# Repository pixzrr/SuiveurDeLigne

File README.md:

# SuiveurDeLigne

## Etape 1 : Créer le PCB
PCB : 100%

Carte imprimée

## Etape 2 : Soudure
Soudure : 100%

Tests : 8/9 validés (89%)

## Etape 3 : Programmation

Création des fonctions tests : terminé

Programmation en logique binaire (principe de sur-correction constante) : terminée

Programmation en logique analogique (s'adapter parfaitement à la courbe en fonction des nuances de gris) : en cours

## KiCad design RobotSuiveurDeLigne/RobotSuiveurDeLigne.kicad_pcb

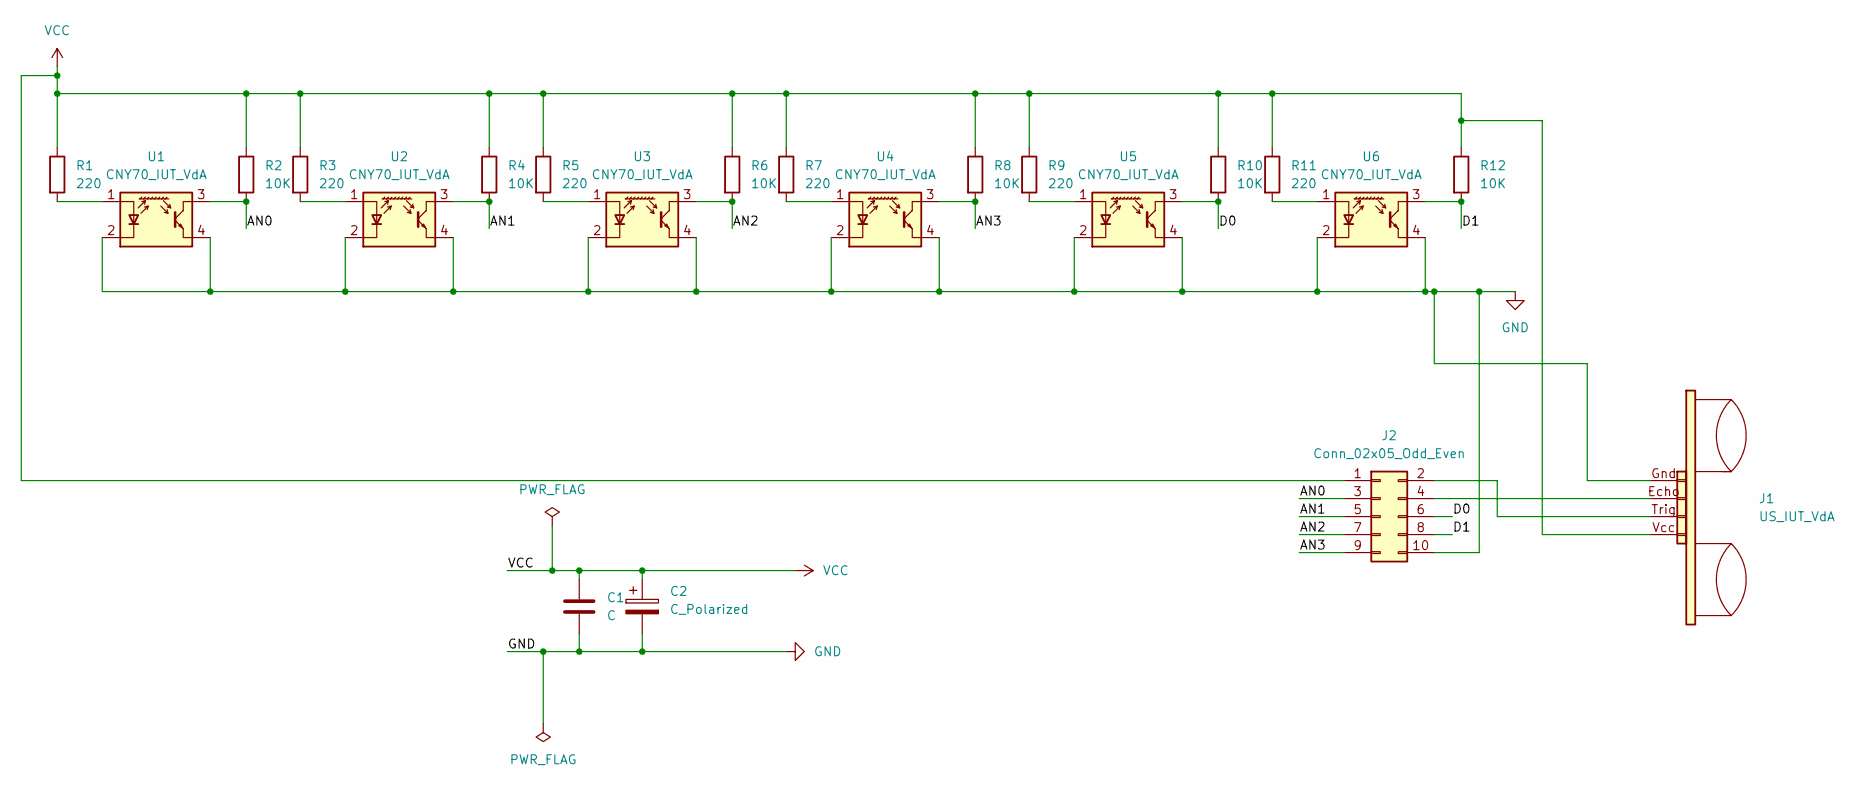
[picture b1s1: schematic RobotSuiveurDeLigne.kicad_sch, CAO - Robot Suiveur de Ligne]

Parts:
C1: C; C_Rect_L7.0mm_W6.5mm_P5.00mm
C2: C_Polarized; CP_Radial_D6.3mm_P2.50mm
J1: US_IUT_VdA; UltraSon_IUT_VdA
J2: Conn_02x05_Odd_Even; IDC-Header_2x05_P2.54mm_Horizontal
R1, R3, R5, R7, R9, R11: 220; R_Axial_DIN0207_L6.3mm_D2.5mm_P10.16mm_Horizontal
R2, R4, R6, R8, R10, R12: 10K; R_Axial_DIN0207_L6.3mm_D2.5mm_P10.16mm_Horizontal
U1, U2, U3, U4, U5, U6: CNY70_IUT_VdA; Vishay_CNY70

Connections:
/AN0: J2.3, R2.2, U1.3 (C)
/AN1: J2.5, R4.2, U2.3 (C)
/AN2: J2.7, R6.2, U3.3 (C)
/AN3: J2.9, R8.2, U4.3 (C)
/D0: J2.6, R10.2, U5.3 (C)
/D1: J2.8, R12.2, U6.3 (C)
GND: C1.2, C2.2, J1.Gnd, J2.10, U1.2 (K), U1.4 (E), U2.2 (K), U2.4 (E), U3.2 (K), U3.4 (E), U4.2 (K), U4.4 (E), U5.2 (K), U5.4 (E), U6.2 (K), U6.4 (E)
unnamed: J1.Trig, J2.2
unnamed: J1.Echo, J2.4
unnamed: R1.2, U1.1 (A)
unnamed: R3.2, U2.1 (A)
unnamed: R5.2, U3.1 (A)
unnamed: R7.2, U4.1 (A)
unnamed: R9.2, U5.1 (A)
unnamed: R11.2, U6.1 (A)
VCC: C1.1, C2.1, J1.Vcc, J2.1, R1.1, R2.1, R3.1, R4.1, R5.1, R6.1, R7.1, R8.1, R9.1, R10.1, R11.1, R12.1

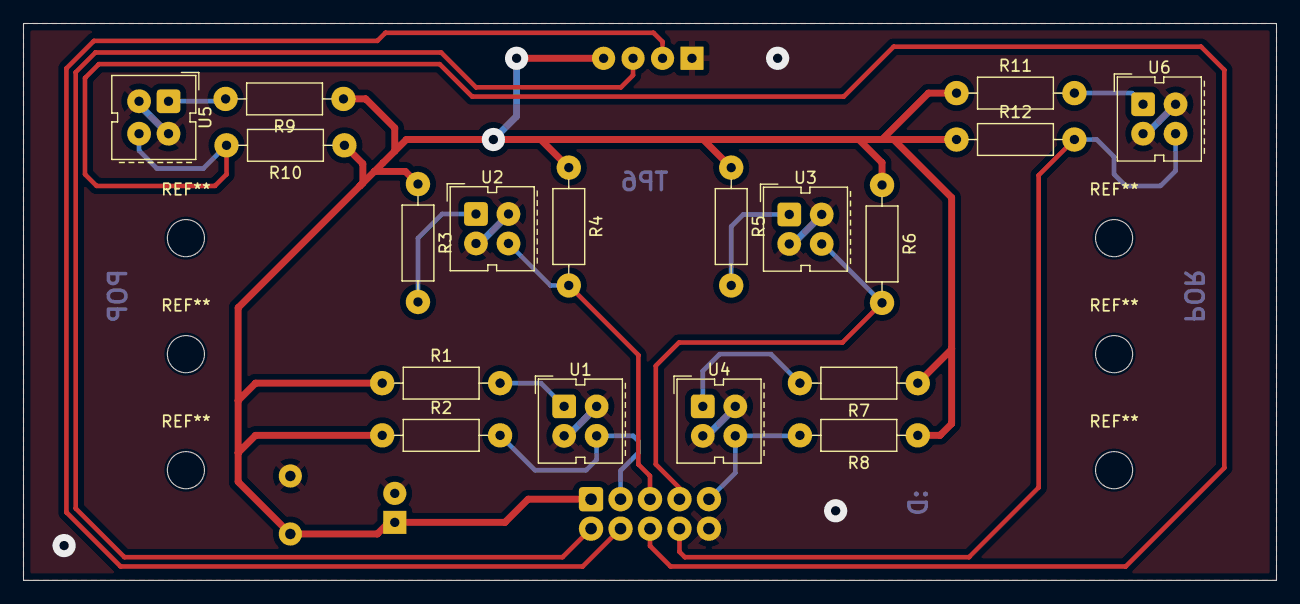
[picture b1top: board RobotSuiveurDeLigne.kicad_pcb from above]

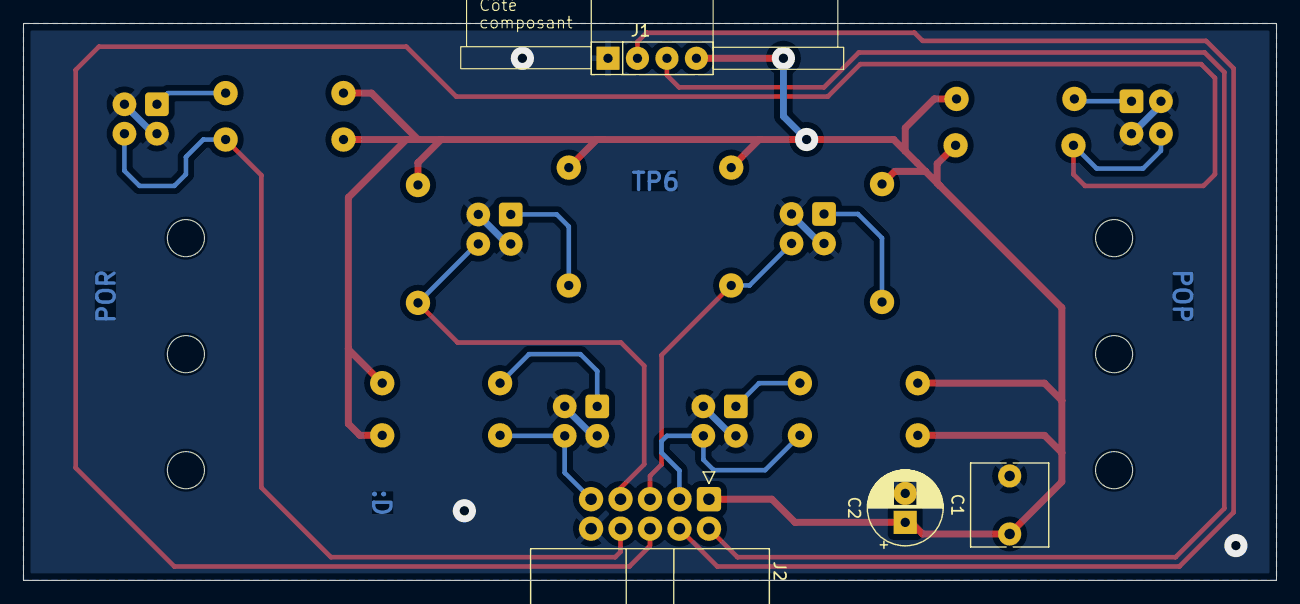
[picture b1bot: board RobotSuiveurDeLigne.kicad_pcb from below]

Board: 2 copper layers, 108.0 x 48.0 mm, 22 parts (4 on the bottom side), 16 nets.

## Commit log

2025-09-15 premier commit
2025-09-15 modifs shéma
2025-09-22 ajout empreintes pour routage
2025-09-24 Test PCB v.1 G
    première version de PCB, G
2025-09-25 Routage V.1.2 G
    Ajustements capteurs + ajout des trous de fixation
2025-09-29 ajouts et changements mineurs
    ajout condensateur + résistances
2025-09-30 1ère version du routagge + changements mineurs
    déplacements de résistances et rotation du capteur U5
2025-10-01 GND retravaillé
2025-10-01 début de l'arrondissement des angles
2025-10-01 revue complète du routage
2025-10-01 ajustement trous de fixation
2025-10-01 léger ajoustement des trous de fixation
2025-10-06 Ajustement de piste
2025-10-06 Version alt du pcb v2.6
2025-10-06 Ajustement Vcc US
    Continuité de la alt_v2.6
2025-10-07 V2.1.7 - Première vérification
2026-01-13 PCB final
    envoyé pour impression
2026-01-13 soudure
2026-01-30 Version binaire
    Programme fonctionnel sur une des deux cartes
2026-01-30 Ajout option test IR analogique
2026-01-30 Ajout fonction rapport vitesse
    Pour tourner en fonction de l'angle de courbure
2026-02-01 Affinage fonction suivre_courbure
    - nouvelle methode : fonction affine
    - déplacement de la fonction vers actions_complexes.cpp +.h
2026-02-02 Version analogique
    tourne bien mais suit pas la ligne
2026-02-02 Correction de l'autonomie des moteurs
    Les moteurs fonctionnaient individuellement, et ne prenaient pas en compte la correction de l'autre moteur, donc j'ai fait une différence pour calculer l'erreur entre les deux mesures. Si = 0, on peu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
2026-02-02 Optimisations
    if (erreur == 0) enlevé, cette condition est inutile, surtout qu'elle ne sera jamais vérifiée (sauf par concours de circonstances)
2026-02-03 corrections
    correction suivi de courbures
    correction marche / arrêt
2026-02-11 Ligne parfaitement suivie
2026-02-16 Ajout et optimisations
    Ajout test obstacles
    Optimisations fonction suivre_courbure();
2026-02-26 optimisations
2026-03-13 ajout 360 v2 + millis
2026-03-23 upd 360 + ajout raccourci
    à tester
2026-03-24 upd 360
2026-03-29 rework raccourci + ajout version m.etats
2026-03-29 amélioration du rework
2026-03-30 modif raccourcis
2026-04-08 Réparation raccourci
2026-04-11 Restructuration finale
    - ajout de commentaires
    - structuration par parties
    - corrections mineures
